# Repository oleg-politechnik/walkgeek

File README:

= About walkgeek ===============================================================

This is walkgeek, another portable music player based upon STM32F4-Discovery
board hardware, which contains STM32F407VGT6 microcontroller and CS43L22 audio
codec. For now, it can play MP3 and Opus files.

The goal of this project is to create a fully functional yet very simple
portable player, optimized for easy navigation across a lot of pretty long audio
files (podcasts).

= Hardware =====================================================================

There are 2 pretty similar HW platforms supported (or rather variations of a
one platform) called N1100 and F4DISCOVERY.

--- F4DISCOVERY ----------------------------------------------------------------

This platform is represented by STM32F4-Discovery board. It gives you an easy
way to try out and develop walkgeek. No HW modifications are necessary in a very
basic case. You only need to put some audio files supported by walkgeek on a USB
Flash drive and attach in to the USB Micro connector (CN5). User interface is
limited to a on-board "User" button which acts as button "3", and 4 leds:
 - Red means no Flash drive connected;
 - Green means Flash drive has enumerated and Player is started;
 - Orange means Player is stopped or loading current track;
 - Blue (blinking) means Player is playing current track.

--- N1100 ----------------------------------------------------------------------

There is also a more portable HW version that fits into Nokia 1100 cell phone
case. Design resources for it are also available in a pcb/ directory of this
project in EAGLE CAD format.

= Software =====================================================================

1. Checkout the latest version of the source code by following the instructions
   here: http://code.google.com/p/walkgeek/source/checkout

2. In order to build the source code, you need:
 - Git
 - CMake of a version of 2.8.4 or higher.
 - ARM GNU Toolchain: CodeSourcery, Linaro, etc.
 
3. You probably will find useful to have openocd as a gdb server which supports
   many cheap JTAG probes, including STLink v2 which is found in all the
   Discovery boards by ST.

= Example steps for Linux-based desktop ========================================

1. Checkout latest version of player's source code.

$ git clone 

2. It seems that CMake doesn't like embedded arm gnu toolchains (which is the
   case for at least CodeSourcery and Linaro on Ubuntu GNU/Linux) and shows
   errors at the project configure stage. You may solve them by typing: 

$ cd walkgeek
$ sudo ./patch_cmake.sh

   Dollar sign stands for command line prompt, do not type it.
   Please note that on OS other than GNU/Linux it may be different file or even
   may be unnecessary. Probably there is more proper way but this one has worked
   for me.

3. You should be at this moment in walkgeek directory. Type:

$ mkdir Build
$ cd Build

4. Next step is to invoke cmake in order to generate Makefiles. You can specify
   a list of parameters where syntax for each item is -D%param_name%=%param_value%.
   Among other standard cmake parameters, you can specify:
   - TOOLCHAIN_PREFIX -- full path to the root directory of your toolchain.
     Default is $ENV{HOME}/Local/gcc-arm-none-eabi-4_6-2012q2
   - TARGET_TRIPLET -- prefic for toolchain programs, default is arm-none-eabi.
   - STM32_USBLib_DIR -- full path to the STM32 USB Host Device Lib.
     Default is ${CMAKE_SOURCE_DIR}/bsp/3rd_party/STM32_USB-Host-Device_Lib_V2.1.0
   - CMAKE_BUILD_TYPE -- Release or Debug or others (please refer to the CMake
     documentation). Default is Debug.

   - PLATFORM -- choose one of the supported HW platforms: N1100, F4DISCOVERY,
     SIMULATOR (see below). Default is N1100.
   - PROFILING -- enable measurement of the CPU consumption of the audio codecs.
     1 enables, 0 disables. Default is 0.
   - ENABLE_TRACE -- enable trace() functions output via USB CDC. Default is 0.
   - USE_MP3 -- enable MP3 support. Default is 0.
   - RPROG_OHM -- if your platform is N1100, this is the value of resistor
     which sets LTC4054 charge current. Default is 2000.
   - SD_CARD_FILE -- if your platform is SIMULATOR, enter a full path to the
     file which contains FAT file system. See below for details. No default here.

   So if your toolchain and paths are the same, you don't need to specify all of
   them. In this example the default values are passed explicitly.

$ cmake -DTOOLCHAIN_PREFIX=/home/oleg/Local/CodeSourcery/Sourcery_CodeBench_Lite_for_ARM_EABI \
-DUSE_MP3=1 ../ -G"Unix Makefiles"

$ make

   Now you can build .hex, .bin or .dis (disassembly) files

$ make walkgeek.hex

   My Ubuntu even auto-completes Makefile targets.

6. (Optional) You can also debug it. Open one console, cd to the walkgeek's
   source root dir and

$ openocd -f openocd_luminary.cfg

   Switch to another console, cd to the walkgeek's source root dir and

$ arm-none-eabi-gdb --quiet --tui -x debug.gdb

= SIMULATOR ====================================================================

  There's a way to launch walkgeek on your PC (currently only POSIX OS'es are
  supported, at least GNU/Linux). PCM Audio output is not yet implemented.
  But console IO works and keyboard is simulated via stdin (just press a key
  and hit enter). If you press a number of keys and press enter, each of them
  will be handled consequently. Also, SD card IO simulation works, so that
  FAT FS module of walkgeek sees no difference compared to real HW. The idea is
  to manually create a file of some MB of a size, create FAT FS inside it
  (just like if it were an SD card), mount it, put some audio or whatever files
  in it and feed it to walkgeek application.

1. To do it, first create a file (this example will create a
   bs*count=128 MB file)

 $ dd if=/dev/zero of=sd_card.bin bs=1024 count=131072
 
2. Make FAT FS here
 
 $ /sbin/mkdosfs -F 16 sd_card.bin
 
3. Mount it
 
 $ mkdir fatmount
 $ sudo mount -t vfat -o umask=0000 -o loop sd_card.bin fatmount
 
4. Put some files into fatmount/ dir.

5. Unmount it in order to drain write buffers.

 $ sudo umount fatmount

6. When launching CMake (see above), choose -DPLATFORM=SIMULATOR -D%path-to%/sd_card.bin

  This is a good way to debug higher-level algorithms (for example, Navigator
  module was tested that way).

Thank you for your attention.

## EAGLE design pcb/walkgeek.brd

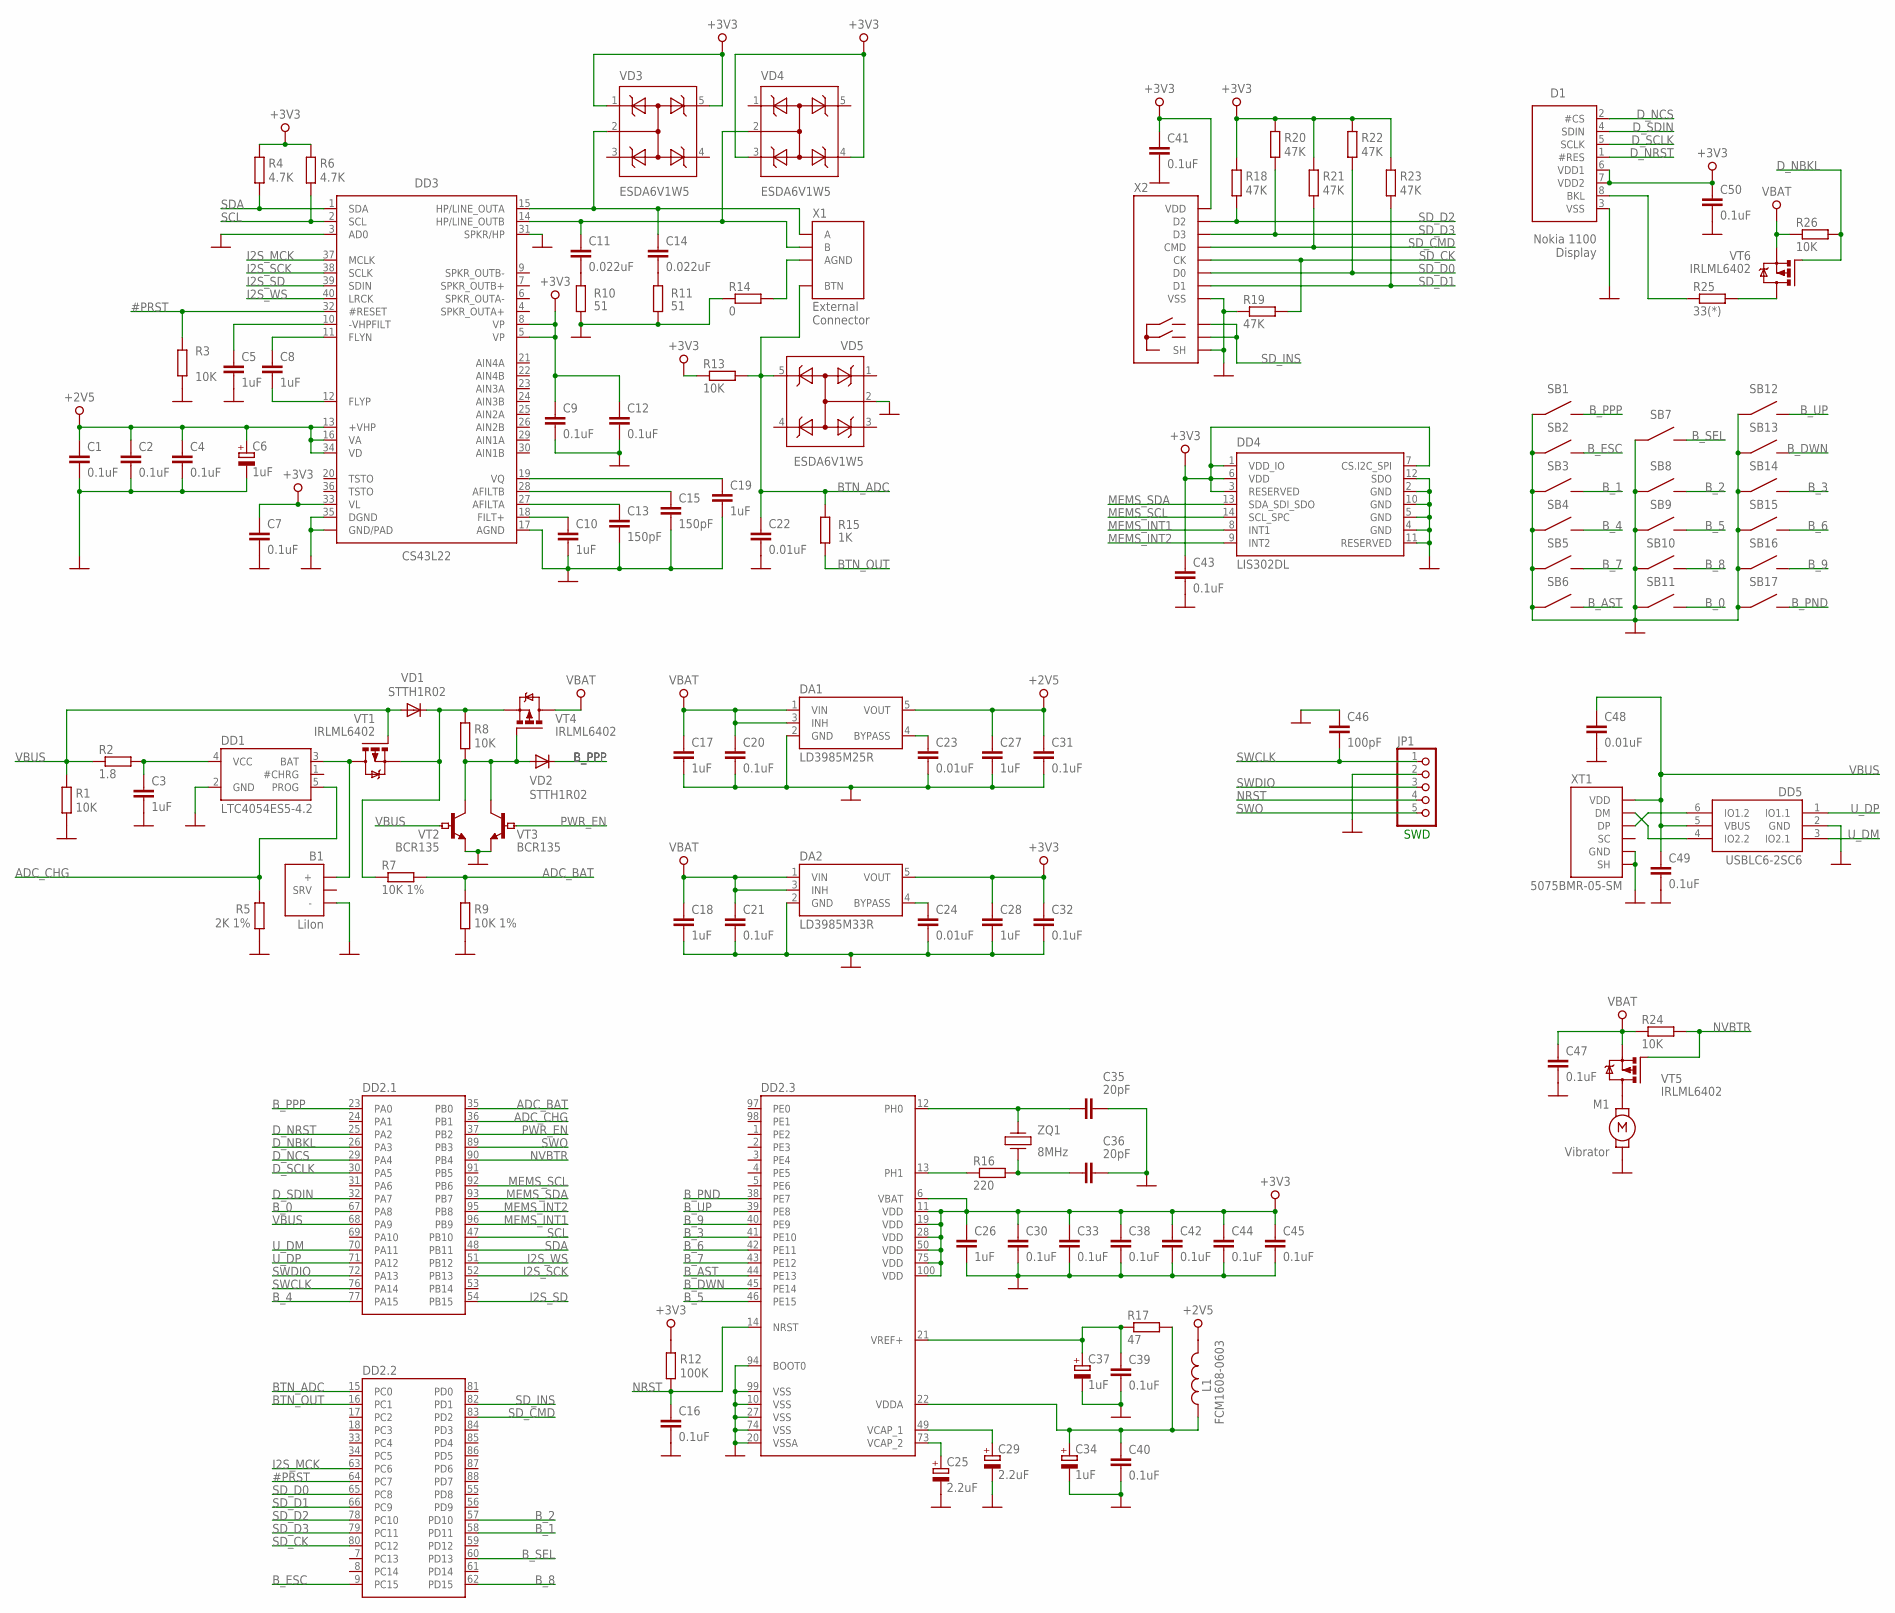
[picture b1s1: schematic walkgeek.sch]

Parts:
B1: NOKIA1100_BATTERY_CONN
C1, C2, C4, C7, C9, C12, C16, C20, C21, C30, C31, C32, C33, C38, C39, C40, C41, C42, C43, C44, C45, C47, C49: 0.1uF; C0402
C3: 1uF; C0805
C5, C8, C10, C17, C18, C19, C26, C27, C28: 1uF; C0603
C6, C34, C37: 1uF; SMC_A
C11, C14: 0.022uF; C0603
C13, C15: 150pF; C0603
C22: 0.01uF; C0805
C23, C24, C48: 0.01uF; C0603
C25, C29: 2.2uF; SMC_A
C35, C36: 20pF; C0603
C46: 100pF; C0805
C50: 0.1uF; C0805
D1: NOKIA1100_DISP
DA1: LD3985M25R; TSOT23-5
DA2: LD3985M33R; TSOT23-5
DD1: LTC4054ES5-4.2; TSOT23-5
DD2: STM32F4XXVXT; LQFP100
DD3: CS43L22; QFN40-6X6
DD4: LIS302DL; LGA14
DD5: USBLC6-2SC6; SOT23-6L
JP1: PINHD-1X5; 1X05/90_FLAT
L1: FCM1608-0603; R0603
M1: NOKIA1100_VIBRATOR
R1, R24, R26: 10K; R0603
R2: 1.8; R1206
R3: 10K; R0402
R4, R6: 4.7K; R0603
R5: 2K 1%; R0805
R7, R9: 10K 1%; R0805
R8, R13: 10K; R0805
R10, R11: 51; R0603
R12: 100K; R0603
R14: 0; R0603
R15: 1K; R0805
R16: 220; R0603
R17: 47; R0603
R18, R19, R20, R21, R22, R23: 47K; R0805
R25: 33(*); R1206
SB1, SB2, SB3, SB4, SB5, SB6, SB7, SB8, SB9, SB10, SB11, SB12, SB13, SB14, SB15, SB16, SB17: NOKIA1100_KEY_PAD_0
VD1, VD2: STTH1R02; SMA
VD3, VD4, VD5: ESDA6V1W5; SOT323-5L
VT1, VT4, VT5, VT6: IRLML6402; MICRO3
VT2, VT3: BCR135; SOT23-BEC
X1: NOKIA1100_EXT_CONN
X2: MICROSD_CONN; TFC-WPCE-08
XT1: 5075BMR-05-SM; 32005-201
ZQ1: 8MHz; QUARTZ_5MM

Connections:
#PRST: DD2.64 (PC7), DD3.32 (#RESET), R3.2
+2V5: C1.1, C2.1, C4.1, C6.+, C27.1, C31.1, DA1.5 (VOUT), DD3.13 (+VHP), DD3.16 (VA), DD3.34 (VD), L1.1
+3V3: C7.1, C9.1, C12.1, C26.1, C28.1, C30.1, C32.1, C33.1, C38.1, C41.1, C42.1, C43.1, C44.1, C45.1, C50.1, D1.6 (VDD1), D1.7 (VDD2), DA2.5 (VOUT), DD2.6 (VBAT), DD2.11 (VDD), DD2.19 (VDD), DD2.28 (VDD), DD2.50 (VDD), DD2.75 (VDD), DD2.100 (VDD), DD3.5 (VP), DD3.8 (VP), DD3.33 (VL), DD4.1 (VDD_IO), DD4.3 (RESERVED), DD4.6 (VDD), DD4.7 (CS.I2C_SPI), R4.2, R6.2, R12.2, R13.1, R18.2, R20.2, R21.2, R22.2, R23.2, VD3.1, VD3.5, VD4.3, VD4.4, X2.VDD
ADC_BAT: DD2.35 (PB0), R7.2, R9.2
ADC_CHG: DD1.5 (PROG), DD2.36 (PB1), R5.2
BTN_ADC: C22.1, DD2.15 (PC0), R13.2, R15.2, VD5.5, X1.BTN
BTN_OUT: DD2.16 (PC1), R15.1
B_0: DD2.67 (PA8), SB11.INNER
B_1: DD2.58 (PD11), SB3.INNER
B_2: DD2.57 (PD10), SB8.INNER
B_3: DD2.41 (PE10), SB14.INNER
B_4: DD2.77 (PA15), SB4.INNER
B_5: DD2.46 (PE15), SB9.INNER
B_6: DD2.42 (PE11), SB15.INNER
B_7: DD2.43 (PE12), SB5.INNER
B_8: DD2.62 (PD15), SB10.INNER
B_9: DD2.40 (PE9), SB16.INNER
B_AST: DD2.44 (PE13), SB6.INNER
B_DWN: DD2.45 (PE14), SB13.INNER
B_ESC: DD2.9 (PC15), SB2.INNER
B_PND: DD2.38 (PE7), SB17.INNER
B_PPP: DD2.23 (PA0), SB1.INNER, VD2.C
B_SEL: DD2.60 (PD13), SB7.INNER
B_UP: DD2.39 (PE8), SB12.INNER
D_NBKL: DD2.26 (PA3), R26.2, VT6.1 (G)
D_NCS: D1.2 (#CS), DD2.29 (PA4)
D_NRST: D1.1 (#RES), DD2.25 (PA2)
D_SCLK: D1.5 (SCLK), DD2.30 (PA5)
D_SDIN: D1.4 (SDIN), DD2.32 (PA7)
GND: B1.-, C1.2, C2.2, C3.2, C4.2, C5.2, C6.-, C7.2, C9.2, C10.2, C12.2, C13.2, C15.2, C16.2, C17.2, C18.2, C19.2, C20.2, C21.2, C22.2, C23.2, C24.2, C25.-, C26.2, C27.2, C28.2, C29.-, C30.2, C31.2, C32.2, C33.2, C34.-, C35.2, C36.2, C37.-, C38.2, C39.2, C40.2, C41.2, C42.2, C43.2, C44.2, C45.2, C46.1, C47.2, C48.2, C49.2, C50.2, D1.3 (VSS), DA1.2 (GND), DA2.2 (GND), DD1.2 (GND), DD2.10 (VSS), DD2.20 (VSSA), DD2.27 (VSS), DD2.74 (VSS), DD2.94 (BOOT0), DD2.99 (VSS), DD3.3 (AD0), DD3.17 (AGND), DD3.31 (SPKR/HP), DD3.35 (DGND), DD3.EXP@3 (GND/PAD), DD3.EXP@4 (GND/PAD), DD3.EXP@5 (GND/PAD), DD3.EXP@9 (GND/PAD), DD4.2 (GND), DD4.4 (GND), DD4.5 (GND), DD4.10 (GND), DD4.11 (RESERVED), DD4.12 (SDO), DD5.2 (GND), JP1.2, M1.2, R1.1, R3.1, R5.1, R9.1, R10.1, R11.1, R14.1, R19.1, SB1.OUTER, SB1.OUTER1 (OUTER), SB2.OUTER, SB2.OUTER1 (OUTER), SB3.OUTER, SB3.OUTER1 (OUTER), SB4.OUTER, SB4.OUTER1 (OUTER), SB5.OUTER, SB5.OUTER1 (OUTER), SB6.OUTER, SB6.OUTER1 (OUTER), SB7.OUTER, SB7.OUTER1 (OUTER), SB8.OUTER, SB8.OUTER1 (OUTER), SB9.OUTER, SB9.OUTER1 (OUTER), SB10.OUTER, SB10.OUTER1 (OUTER), SB11.OUTER, SB11.OUTER1 (OUTER), SB12.OUTER, SB12.OUTER1 (OUTER), SB13.OUTER, SB13.OUTER1 (OUTER), SB14.OUTER, SB14.OUTER1 (OUTER), SB15.OUTER, SB15.OUTER1 (OUTER), SB16.OUTER, SB16.OUTER1 (OUTER), SB17.OUTER, SB17.OUTER1 (OUTER), VD5.2, VT2.E, VT3.E, X2.SH1 (SH), X2.SH2 (SH), X2.SH3 (SH), X2.SH4 (SH), X2.VSS, XT1.5 (GND), XT1.M1 (SH), XT1.M2 (SH), XT1.M3 (SH), XT1.M4 (SH)
I2S_MCK: DD2.63 (PC6), DD3.37 (MCLK)
I2S_SCK: DD2.52 (PB13), DD3.38 (SCLK)
I2S_SD: DD2.54 (PB15), DD3.39 (SDIN)
I2S_WS: DD2.51 (PB12), DD3.40 (LRCK)
MEMS_INT1: DD2.96 (PB9), DD4.8 (INT1)
MEMS_INT2: DD2.95 (PB8), DD4.9 (INT2)
MEMS_SCL: DD2.92 (PB6), DD4.14 (SCL_SPC)
MEMS_SDA: DD2.93 (PB7), DD4.13 (SDA_SDI_SDO)
unnamed: D1.8 (BKL), R25.1
unnamed: C10.1, DD3.18 (FILT+)
unnamed: C13.1, DD3.27 (AFILTA)
unnamed: C15.1, DD3.28 (AFILTB)
unnamed: C19.1, DD3.19 (VQ)
unnamed: C11.1, DD3.14 (HP/LINE_OUTB), VD4.2, X1.B
unnamed: C14.1, DD3.15 (HP/LINE_OUTA), VD3.2, X1.A
unnamed: C8.1, DD3.11 (FLYN)
unnamed: C8.2, DD3.12 (FLYP)
unnamed: C5.1, DD3.10 (-VHPFILT)
unnamed: R14.2, X1.AGND
unnamed: C11.2, R10.2
unnamed: C14.2, R11.2
unnamed: M1.1, VT5.3 (D)
unnamed: C3.1, DD1.4 (VCC), R2.2
unnamed: R7.1, R8.2, VD1.C, VT1.2 (S), VT4.2 (S)
unnamed: DD2.13 (PH1), R16.1
unnamed: R25.2, VT6.3 (D)
unnamed: R8.1, VD2.A, VT2.C, VT3.C, VT4.1 (G)
unnamed: DD5.6 (IO1.2), XT1.3 (DP)
unnamed: DD5.4 (IO2.2), XT1.2 (DM)
unnamed: C25.+, DD2.73 (VCAP_2)
unnamed: C35.1, DD2.12 (PH0), ZQ1.P$1
unnamed: C24.1, DA2.4 (BYPASS)
unnamed: C23.1, DA1.4 (BYPASS)
unnamed: C29.+, DD2.49 (VCAP_1)
unnamed: C34.+, C40.1, DD2.22 (VDDA), L1.2, R17.2
unnamed: C37.+, C39.1, DD2.21 (VREF+), R17.1
unnamed: C36.1, R16.2, ZQ1.P$2
NRST: C16.1, DD2.14 (NRST), JP1.4, R12.1
NVBTR: DD2.90 (PB4), R24.2, VT5.1 (G)
PWR_EN: DD2.37 (PB2), VT3.B
SCL: DD2.47 (PB10), DD3.2 (SCL), R6.1
SDA: DD2.48 (PB11), DD3.1 (SDA), R4.1
SD_CK: DD2.80 (PC12), R19.2, X2.CLK (CK)
SD_CMD: DD2.83 (PD2), R21.1, X2.CMD
SD_D0: DD2.65 (PC8), R22.1, X2.DAT0 (D0)
SD_D1: DD2.66 (PC9), R23.1, X2.DAT1 (D1)
SD_D2: DD2.78 (PC10), R18.1, X2.DAT2 (D2)
SD_D3: DD2.79 (PC11), R20.1, X2.CD/DAT3 (D3)
SD_INS: DD2.82 (PD1), X2.SNS1, X2.SNS2
SWCLK: C46.2, DD2.76 (PA14), JP1.1
SWDIO: DD2.72 (PA13), JP1.3
SWO: DD2.89 (PB3), JP1.5
U_DM: DD2.70 (PA11), DD5.3 (IO2.1)
U_DP: DD2.71 (PA12), DD5.1 (IO1.1)
VBAT: C17.1, C18.1, C20.1, C21.1, C47.1, DA1.1 (VIN), DA1.3 (INH), DA2.1 (VIN), DA2.3 (INH), R24.1, R26.1, VT4.3 (D), VT5.2 (S), VT6.2 (S)
VBAT0: B1.+, DD1.3 (BAT), VT1.3 (D)
VBUS: C48.1, C49.1, DD2.68 (PA9), DD5.5 (VBUS), R1.2, R2.1, VD1.A, VT1.1 (G), VT2.B, XT1.1 (VDD)

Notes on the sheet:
SWD

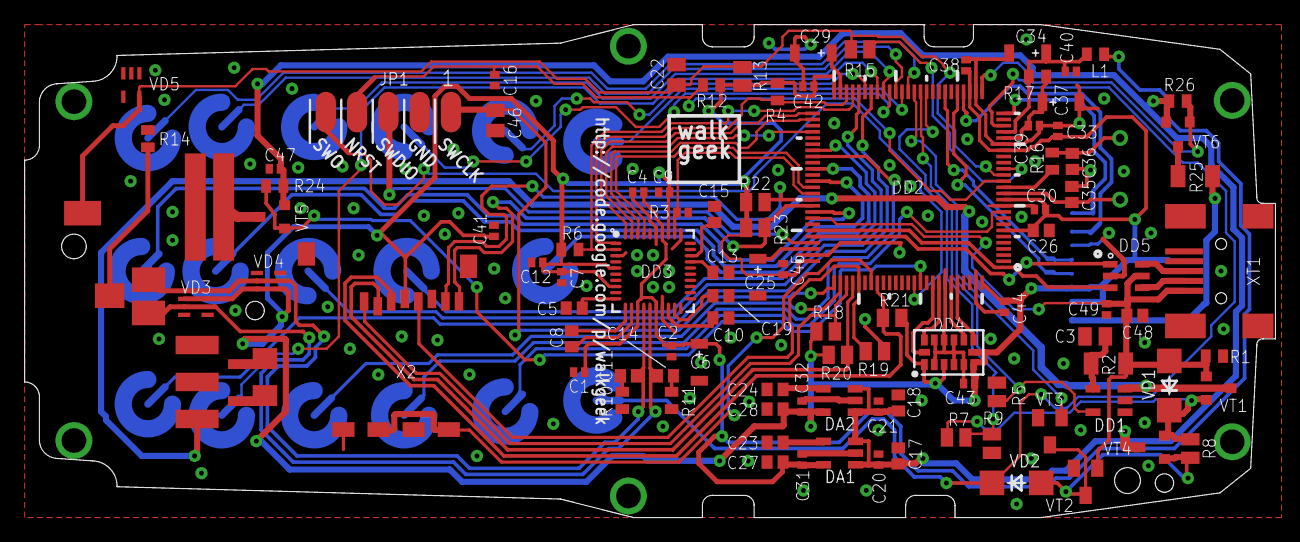
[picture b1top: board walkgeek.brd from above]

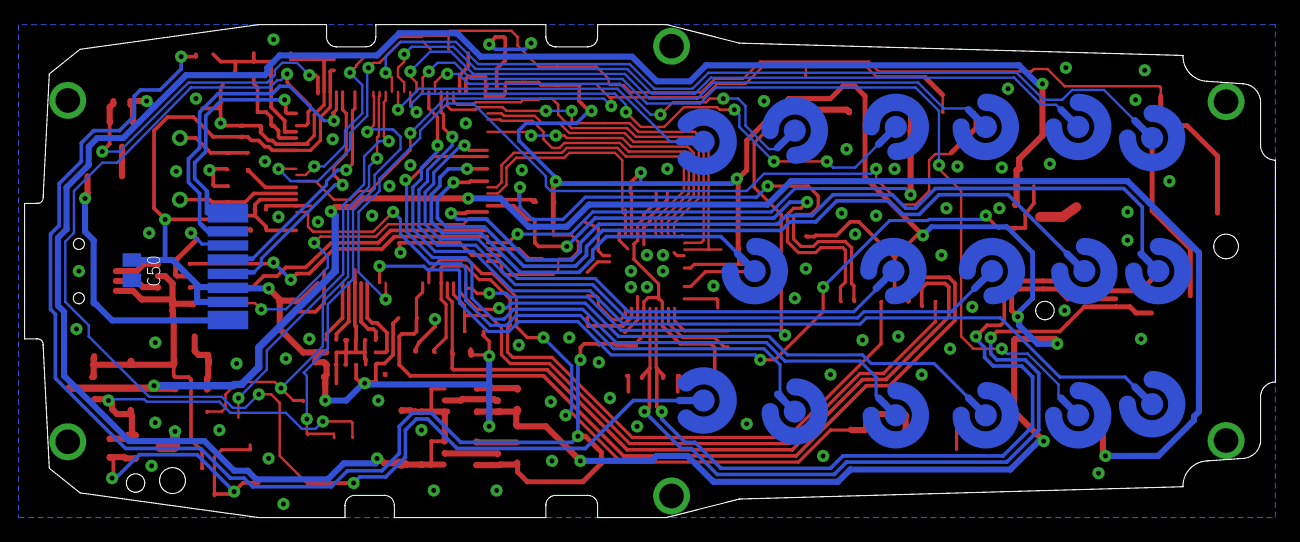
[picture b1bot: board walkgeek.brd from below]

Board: 2 copper layers, 101.5 x 40.0 mm, 120 parts (19 on the bottom side), 87 nets.

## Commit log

2013-04-22 v1.0 pcb draft
2013-08-01 Initial source code commit (m4-player svn r9)
2013-08-01 Initial port to 1100 platform
2013-08-01 Ported OPUS
2013-08-01 player first/last file in current dir
2013-08-01 Added STM32F4DISCOVERY board port
2013-08-01 Navigator fixes
2013-08-01 PowerManager fixes
2013-08-01 Moved user heap to CCM
2013-08-01 trunk
2013-08-01 Scheduler RemoveTask fix
2013-08-01 Corrected pcb numbering and captions
2013-08-01 Initial transition to FreeRTOS
2013-08-01 Everything works, but FAT FS is non-reentrant yet
2013-08-01 Added SD card locks. Still observe a bug with SDIO lib which needs intermediate buffering
2013-08-01 tasks
2013-08-01 some mp3's does lag
2013-08-01 Fixed: ini file quoted paths, RPROG_OHM parameter error
2013-08-01 not working FS
2013-08-01 debugging stalled mfile
2013-08-08 Fixed OPUS track load time
2013-08-08 Newer UI engine + various fixes
2013-08-13 Fixed FF and screen updates. Removed Audio_Stop call between tracks.
2013-08-19 Optimized GUI and serialized variable updates
2013-08-19 Changed tick interval to 10ms
2013-09-06 UI Fixes. Added auto-pause and auto-resume feature if headset is pulled out while playing
2014-02-22 flags.cmake
2014-02-23 Display divided into 2 layers; bug fixes
2015-03-15 Fixed recursive interrupt enable bug
2015-03-15 Migrating wiki contents from Google Code
2015-03-19 LICENSE added
2015-03-31 Create gh-pages branch via GitHub
